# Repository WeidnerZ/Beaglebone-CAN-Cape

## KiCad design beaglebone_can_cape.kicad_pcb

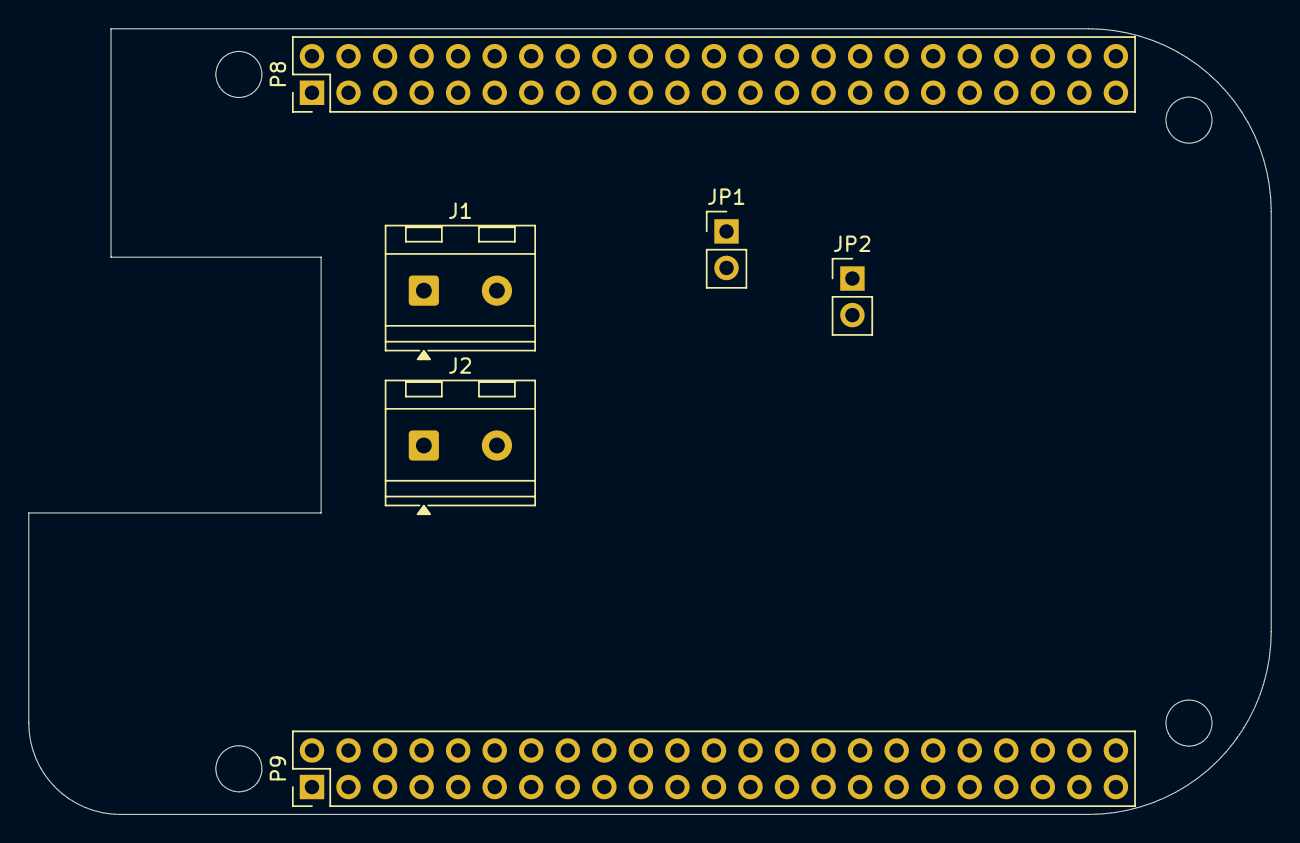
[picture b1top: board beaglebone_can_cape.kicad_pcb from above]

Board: 2 copper layers, 86.4 x 54.6 mm, 10 parts (0 on the bottom side), 6 nets, no tracks yet.

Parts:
J1: DCAN0; TerminalBlock_RND_205-00232_1x02_P5.08mm_Horizontal
J2: DCAN1; TerminalBlock_RND_205-00232_1x02_P5.08mm_Horizontal
JP1, JP2: Jumper_2_Open; PinHeader_1x02_P2.54mm_Vertical
MH1, MH2, MH3, MH4: MountingHole_3.2mm_M3_DIN965
P8, P9: BeagleBone_Black_Header; PinHeader_2x23_P2.54mm_Vertical

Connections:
+3V3: P9.3, P9.4
+5V: P9.5, P9.6
GNDD: P8.1, P8.2, P9.1, P9.2, P9.43, P9.44, P9.45, P9.46
unnamed: J1.2, JP1.1 (A)
unnamed: J2.2, JP2.1 (A)
VBUS: P9.7, P9.8

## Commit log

2026-01-26 finished sch, adding footprints now
2026-01-31 Had to fork to commit (no write access to main)
2026-02-01 test push
